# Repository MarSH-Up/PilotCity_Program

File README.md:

# PilotCity_Program

Hi Guys, here you are going to find the material to complete the basic introduction to Eagle Autodesk for the PilotCity program, We hope that you enjoy the process, and please feel free to send me an email, if you have any issue or doubts, to mario.dh@seeed.cc .

You can access to the simulation here:
<a href=https://www.multisim.com/content/UM945De29GwHbnXSL4hLWn/555-blinky/ target="_blank">
	<br>Multisim Live: 555 blinky
</a>
So you can see what we expect the circuit do once you have it finished.

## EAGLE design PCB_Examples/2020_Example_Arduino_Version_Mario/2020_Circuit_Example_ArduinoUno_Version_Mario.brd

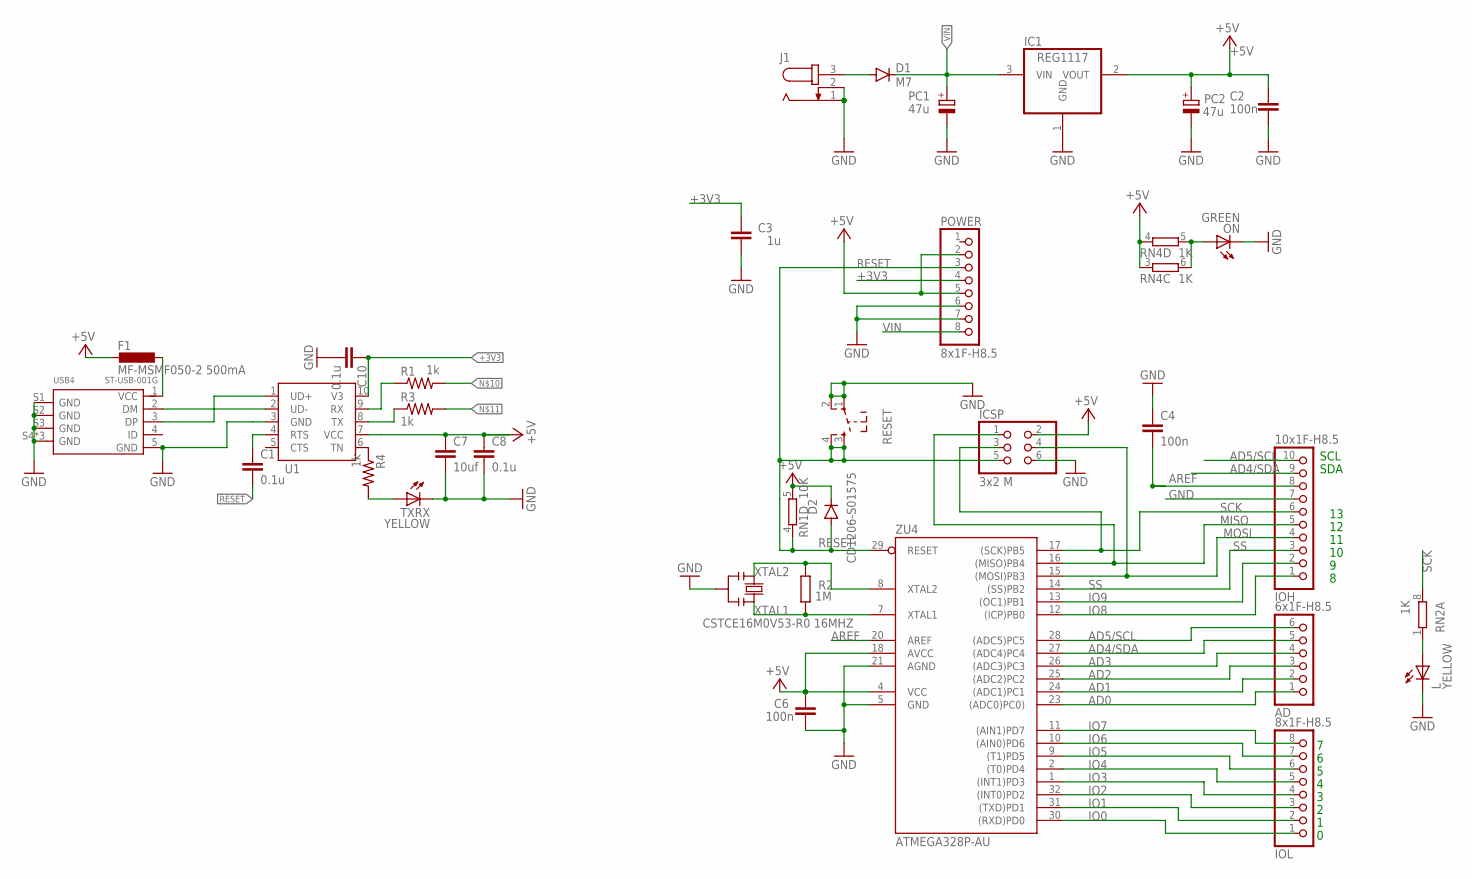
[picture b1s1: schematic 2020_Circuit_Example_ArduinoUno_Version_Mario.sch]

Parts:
AD: 6x1F-H8.5; 1X06
C1, C8, C10: 0.1u; C0805
C2, C6: 100n; C0603-ROUND
C3: 1u; C0603-ROUND
C4: 100n; C0805
C7: 10uf; C0805
D1: M7; SMB
D2: CD1206-S01575; MINIMELF
F1: MF-MSMF050-2 500mA; L1812
IC1: REG1117; SOT223
ICSP: 3x2 M; 2X03
IOH: 10x1F-H8.5; 1X10
IOL: 8x1F-H8.5; 1X08
J1: JACK-PLUG0; SPC4077
L: YELLOW; CHIP-LED0805
ON: GREEN; CHIP-LED0805
PC1, PC2: 47u; PANASONIC_D
POWER: 8x1F-H8.5; 1X08
R1, R3, R4: 1k; M0805
R2: 1M; R0603-ROUND
RESET: SW_TACT_4P; SW_TACT_SMALL
RN1: 10K; CAY16
RN2, RN4: 1K; CAY16
TXRX: YELLOW; CHIP-LED0805
U1: CH340ESMD; MSOP10
USB4: ST-USB-001G; MICRO-USB5+4P-SMD-0.65-B
Y2: CSTCE16M0V53-R0 16MHZ; RESONATOR
ZU4: ATMEGA328P-AU; TQFP32-08

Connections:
+3V3: C3.2, C10.1, POWER.4, U1.10 (V3)
+5V: C2.2, C6.2, C7.1, C8.1, D2.C, F1.2, IC1.2 (VOUT), ICSP.2, PC2.+, POWER.2, POWER.5, RN1.5 (2), RN4.3 (1), RN4.4 (1), U1.7 (VCC), ZU4.4 (VCC), ZU4.18 (AVCC)
AD0: AD.1, ZU4.23 ((ADC0)PC0))
AD1: AD.2, ZU4.24 ((ADC1)PC1)
AD2: AD.3, ZU4.25 ((ADC2)PC2)
AD3: AD.4, ZU4.26 ((ADC3)PC3)
AD4/SDA: AD.5, IOH.9, ZU4.27 ((ADC4)PC4)
AD5/SCL: AD.6, IOH.10, ZU4.28 ((ADC5)PC5)
AREF: C4.2, IOH.8, ZU4.20 (AREF)
GND: C2.1, C3.1, C4.1, C6.1, C7.2, C8.2, C10.2, IC1.1 (GND), ICSP.6, IOH.7, J1.1, J1.2, L.C, ON.C, PC1.-, PC2.-, POWER.6, POWER.7, RESET.1, RESET.2, TXRX.C, U1.3 (GND), USB4.5 (GND), USB4.S1 (GND), USB4.S2 (GND), USB4.S3 (GND), USB4.S4 (GND), USB4.S5 (GND), USB4.S6 (GND), Y2.2, ZU4.5 (GND), ZU4.21 (AGND)
IO0: IOL.1, ZU4.30 ((RXD)PD0)
IO1: IOL.2, ZU4.31 ((TXD)PD1)
IO2: IOL.3, ZU4.32 ((INT0)PD2)
IO3: IOL.4, ZU4.1 ((INT1)PD3)
IO4: IOL.5, ZU4.2 ((T0)PD4)
IO5: IOL.6, ZU4.9 ((T1)PD5)
IO6: IOL.7, ZU4.10 ((AIN0)PD6)
IO7: IOL.8, ZU4.11 ((AIN1)PD7)
IO8: IOH.1, ZU4.12 ((ICP)PB0)
IO9: IOH.2, ZU4.13 ((OC1)PB1)
MISO: ICSP.1, IOH.5, ZU4.16 ((MISO)PB4)
MOSI: ICSP.4, IOH.4, ZU4.15 ((MOSI)PB3)
unnamed: L.A, RN2.1
unnamed: U1.2 (UD-), USB4.2 (DM)
unnamed: ON.A, RN4.5 (2), RN4.6 (2)
unnamed: U1.1 (UD+), USB4.3 (DP)
unnamed: D1.A, J1.3
unnamed: F1.1, USB4.1 (VCC)
unnamed: C1.1, U1.4 (RTS)
unnamed: R1.1, U1.9 (RX)
unnamed: R3.1, U1.8 (TX)
unnamed: R4.1, U1.6 (TN)
unnamed: R4.2, TXRX.A
RESET: C1.2, D2.A, ICSP.5, POWER.3, RESET.3, RESET.4, RN1.4 (1), ZU4.29 (RESET)
SCK: ICSP.3, IOH.6, RN2.8 (2), ZU4.17 ((SCK)PB5)
SS: IOH.3, ZU4.14 ((SS)PB2)
VIN: D1.C, IC1.3 (VIN), PC1.+, POWER.8
XTAL1: R2.1, Y2.3, ZU4.7 (XTAL1)
XTAL2: R2.2, Y2.1, ZU4.8 (XTAL2)

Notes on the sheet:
SDA
SCL

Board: 2 copper layers, 35 parts (0 on the bottom side), 39 nets, no tracks yet.

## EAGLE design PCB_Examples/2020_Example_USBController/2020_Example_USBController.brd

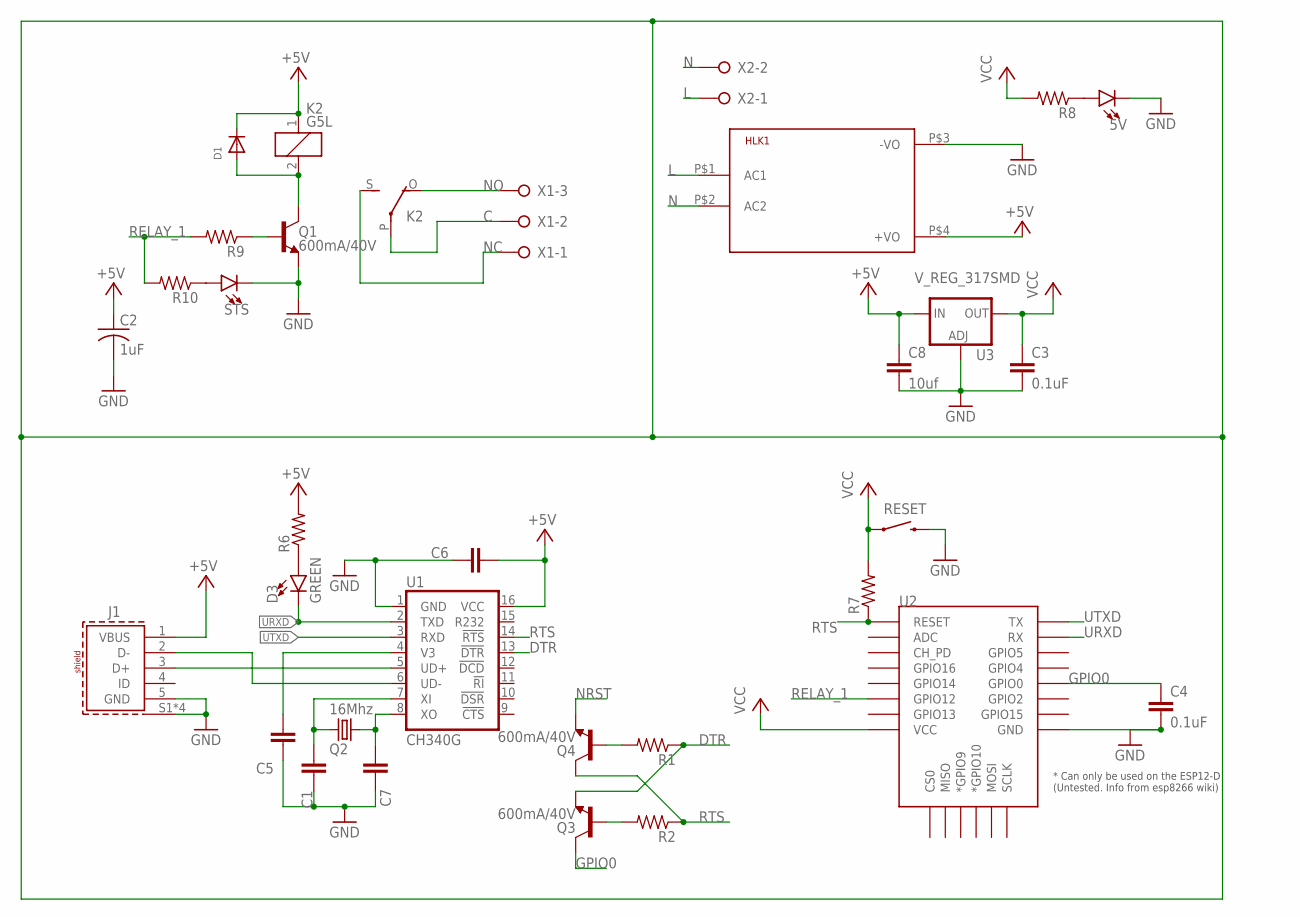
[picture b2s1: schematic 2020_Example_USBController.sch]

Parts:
5V: LED-GREEN0603; LED-0603
C1, C7: 10pF; C0805
C2: 1uF; C0805K
C3, C4, C6: 0.1uF; C0805
C5: 10nF; C0805
C8: 10uf; C0805
D1: DIODESOD-123; SOD-123
D3: GREEN; LED-0603
HLK1: HLK-PM013W; HLK-PM01
J1: 629105150521
K2: G5L; G5LE
Q1, Q3, Q4: 600mA/40V; SOT23-3
Q2: 16Mhz; 5032/2P
R1, R2, R6, R7, R8, R9, R10: R-US_R0805; R0805
RESET: RS032G05A3SM-SPST-MOMENTARY-SWSMD-1101NE; TACTILE-SWITCH-1101NE
STS: LED-GREEN0603; LED-0603
U1: CH340G; SO016
U2: ESP12ESMD; ESP12E-SMD
U3: V_REG_317SMD; SOT223
X1: W237-03P; W237-133
X2: W237-02P; W237-132

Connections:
+5V: C2.1, C6.2, C8.1, D1.C, HLK1.P$4 (+VO), J1.1 (VBUS), K2.1, R6.2, U1.16 (VCC), U3.3 (IN)
C: K2.P, X1.2
DTR: Q3.2 (E), R1.1, U1.13 (!DTR)
GND: 5V.C, C1.1, C2.2, C3.2, C4.2, C5.1, C6.1, C7.1, C8.2, HLK1.P$3 (-VO), J1.5 (GND), J1.S1 (SHIELD), J1.S2 (SHIELD), J1.S3 (SHIELD), J1.S4 (SHIELD), Q1.2 (E), RESET.2, STS.C, U1.1 (GND), U2.GND, U3.1 (ADJ)
GPIO0: C4.1, Q3.3 (C), U2.GPIO0
L: HLK1.P$1 (AC1), X2.1
N: HLK1.P$2 (AC2), X2.2
unnamed: D3.A, R6.1
unnamed: D1.A, K2.2, Q1.3 (C)
unnamed: J1.3 (D+), U1.5 (UD+)
unnamed: Q1.1 (B), R9.1
unnamed: J1.2 (D-), U1.6 (UD-)
unnamed: C7.2, Q2.2, U1.8 (XO)
unnamed: R10.1, STS.A
unnamed: 5V.A, R8.1
unnamed: Q4.1 (B), R1.2
unnamed: Q3.1 (B), R2.2
unnamed: C1.2, Q2.1, U1.7 (XI)
NC: K2.S, X1.1
NO: K2.O, X1.3
NRST: Q4.2 (E)
RELAY_1: R9.2, R10.2, U2.GPIO12
RTS: Q4.3 (C), R2.1, R7.1, U1.14 (!RTS), U2.RESET
URXD: D3.C, U1.2 (TXD), U2.RXD0 (RX)
UTXD: U1.3 (RXD), U2.TXD0 (TX)
V1: C5.2, U1.4 (V3)
VCC: C3.1, R7.2, R8.2, RESET.1, U2.VCC, U3.2 (OUT)

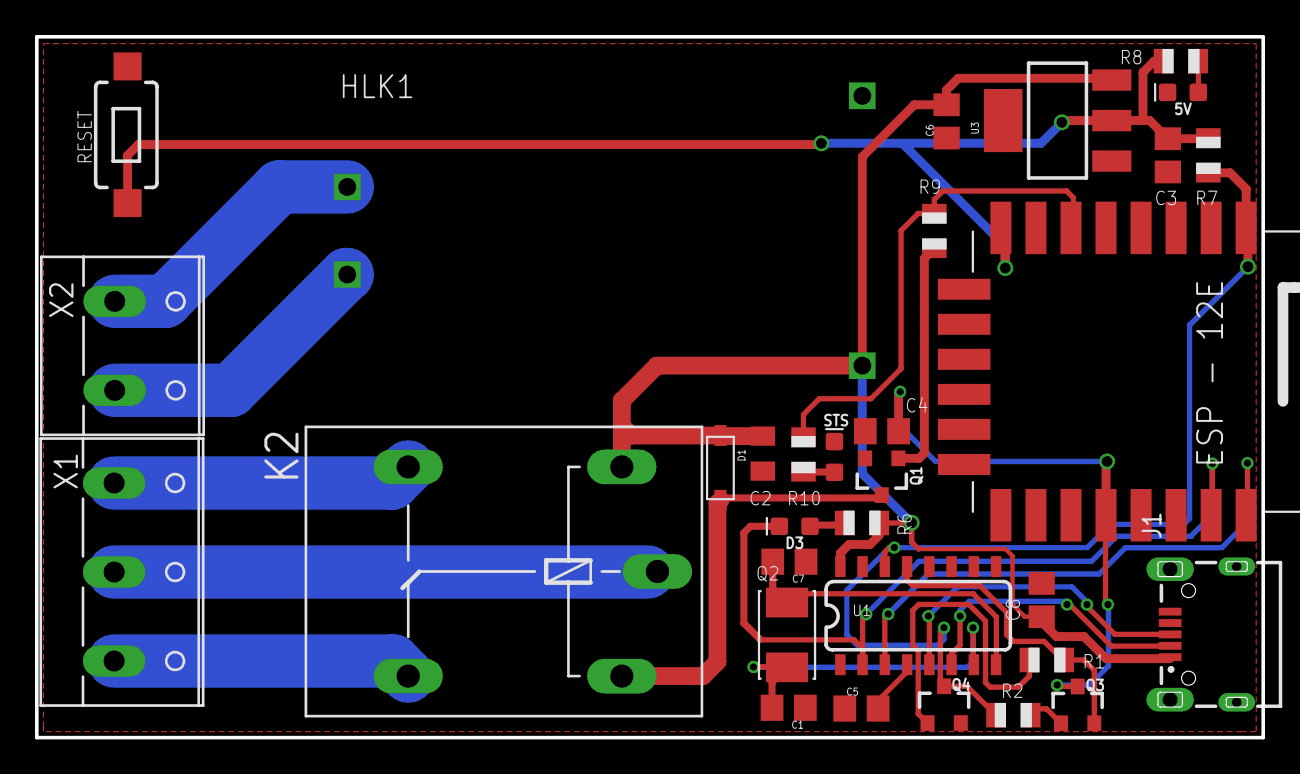
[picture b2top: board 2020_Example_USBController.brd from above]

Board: 2 copper layers, 70.0 x 40.0 mm, 32 parts (0 on the bottom side), 26 nets.

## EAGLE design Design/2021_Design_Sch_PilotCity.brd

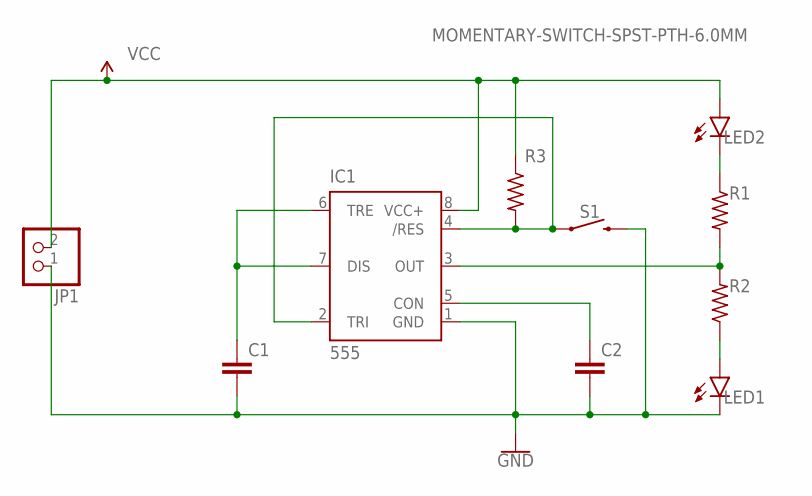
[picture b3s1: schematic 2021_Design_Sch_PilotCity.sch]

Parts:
C1, C2: C5/7.2; C5B7.2
IC1: 555; DIP08-KIT
JP1: PINHD-1X2; 1X02
LED1, LED2: LEDB156; Q62902-B156
R1, R2, R3: R-US_0207/10; 0207/10
S1: MOMENTARY-SWITCH-SPST-PTH-6.0MM; TACTILE_SWITCH_PTH_6.0MM

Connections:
GND: C1.2, C2.2, IC1.1 (GND), JP1.1, LED1.K (C), S1.3 (2)
unnamed: LED2.K (C), R1.1
unnamed: LED1.A, R2.1
unnamed: IC1.3 (OUT), R1.2, R2.2
unnamed: C1.1, IC1.6 (TRE), IC1.7 (DIS)
unnamed: C2.1, IC1.5 (CON)
unnamed: IC1.2 (TRI), IC1.4 (/RES), R3.2, S1.1
VCC: IC1.8 (VCC+), JP1.2, LED2.A, R3.1

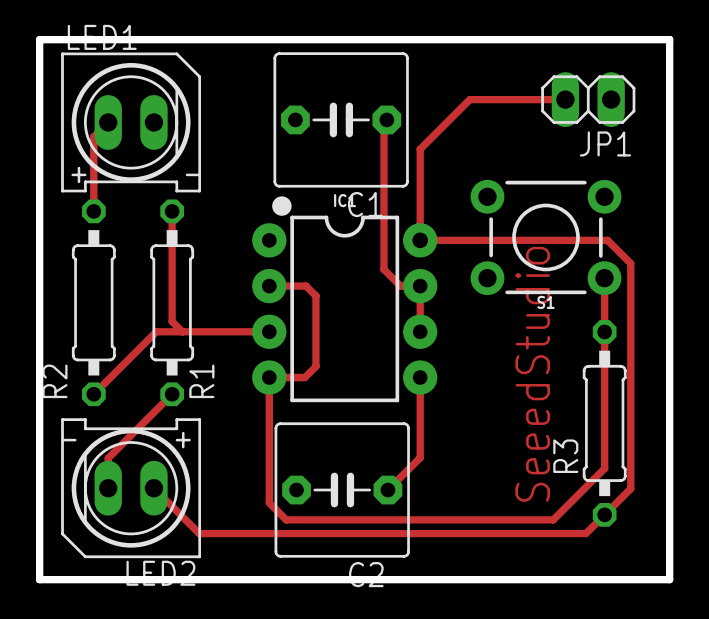
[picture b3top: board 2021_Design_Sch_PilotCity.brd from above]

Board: 2 copper layers, 35.0 x 30.0 mm, 10 parts (0 on the bottom side), 8 nets.

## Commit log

2021-02-24 Create Design_Files
2021-02-24 Create 2020_Example_USBController

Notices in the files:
parts and their libraries:
SparkFun-IC-Special-Function: Licensing: Creative Commons ShareAlike 4.0 International - https://creativecommons.org/licenses/by-sa/4.0
Wurth_Connectors_WR-USB: Copyright: Würth Elektronik
